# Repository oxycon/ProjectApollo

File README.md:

# ProjectApollo
This Github repository contains Designs/docs/software/PCB for Project Apollo (open source oxygen concentrator)

For more context behind the history/goals/motivation for this project please see our coverage in Helpful Engineering blog: 
- https://www.helpfulengineering.org/projects-news/project-spotlight-apollo-oxygen-concentrator/  

<b style='color:red'>Update</b>: check out our  presentation at RespiCon 2021! 
- https://github.com/oxycon/ProjectApollo/blob/master/docs/Project%20Apollo%20RespiCon%20v11.pdf

## Apollo v2 build instructions
- https://github.com/oxycon/ProjectApollo/blob/master/prototypes/Apollo%20v2/docs/Building%20instructions%20-%20prototype%20v2.pdf 

## Why
- Ventilators need oxygen! (typical FiO2 0.4 … 0.9)
- Oxygen generation is a big problem in developing countries. 
  - No established infrastructure. 
  - Oxygen bottles are expensive
- People are already looking at alternative (local) ways for producing oxygen
## What 
- Goal of the Apollo prototype = enabling people around the world to build the prototype as fast as possible
- Focus = Simplicity and speed of build 
- Final goal = Enable people to iterate and publish their own designs in the community
## How
- Follow the published build documentation
- Buy/source the materials (check out the BOM)
- Build the prototype
- Validate O2 concentration and flow. Use a good O2 and flow sensor. 
- Think about risk analysis and assessment: template for Apollo-derived design
- Document and iterate your own design. Publish your findings to the community! 

## Target 
- Output medical grade Oxygen ideally at 93% 
- Flow rate of 1-20 liters per minute (5 l/m being standard for oxygen therapy)

## Building instructions (prototype v2)
- Achieves O2 concentration out of the box: around 45% @ 5 liters/min (enough for less-critical ventilator use cases)
- Instructables-style (step-by-step) build instructions: https://github.com/oxycon/ProjectApollo/blob/master/prototypes/Apollo%20v2/docs/Building%20instructions%20-%20prototype%20v2.pdf 
- Bill of materials: https://github.com/oxycon/ProjectApollo/tree/master/prototypes/Apollo%20v2/BOM 

## Youtube videos
- Prototype v1 (old): https://www.youtube.com/playlist?list=PL34ykrB-qW7VGt1Hwd10Zb3s1eCDftkK8 
- Prototype v2 (latest): https://www.youtube.com/playlist?list=PL34ykrB-qW7X6d74_VnCFfBaVkm8pQXZK

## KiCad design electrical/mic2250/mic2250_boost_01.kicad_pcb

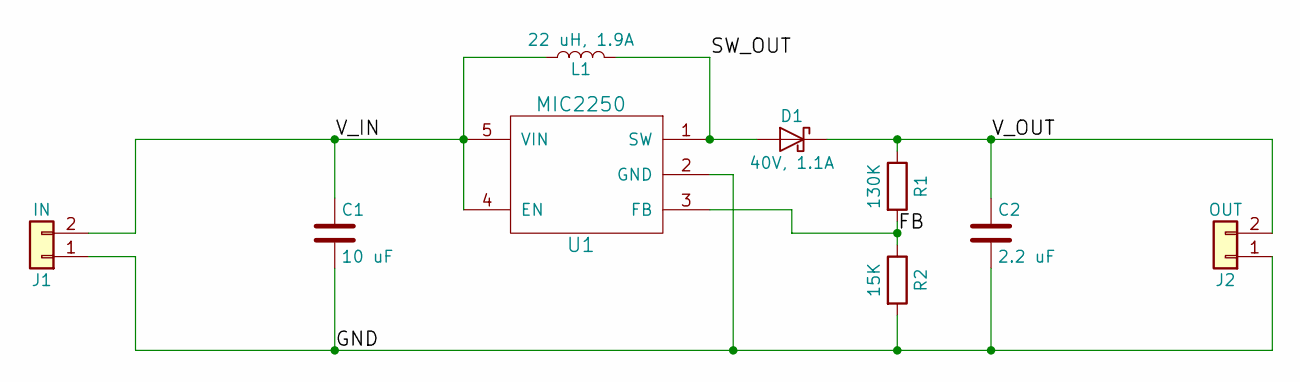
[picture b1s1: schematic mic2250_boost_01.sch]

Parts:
C1: 10 uF; C_1206
C2: 2.2 uF; C_1206
D1: 40V, 1.1A; do219ab
J1: IN; Pin_Header_Straight_1x02_Pitch2.54mm
J2: OUT; Pin_Header_Straight_1x02_Pitch2.54mm
L1: 22 uH, 1.9A; MURATA-DG6050C
R1: 130K; R_0805
R2: 15K; R_0805
U1: MIC2250; SOT-753_(TSOP-5)_Handsoldering

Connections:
/FB: R1.2, R2.1, U1.3 (FB)
/GND: C1.2, C2.2, J1.1, J2.1, R2.2, U1.2 (GND)
/SW_OUT: D1.2 (A), L1.2, U1.1 (SW)
/V_IN: C1.1, J1.2, L1.1, U1.4 (EN), U1.5 (VIN)
/V_OUT: C2.1, D1.1 (K), J2.2, R1.1

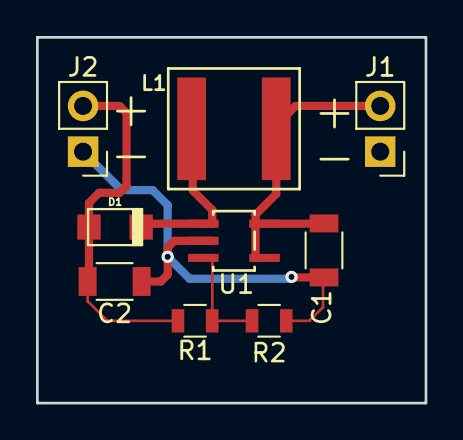
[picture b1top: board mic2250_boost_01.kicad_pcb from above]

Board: 2 copper layers, 21.6 x 20.3 mm, 9 parts (0 on the bottom side), 5 nets.

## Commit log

2020-03-18 add license
2020-03-20 Combined commit
2020-03-22 add Arduino source code for valve cycling
2020-03-22 move file in prototype subdirectory
2020-03-22 comments/fixes
2020-03-22 comments/fixes 2
2020-03-22 fix materials
2020-03-22 add schematic
2020-03-22 add PDF exports
2020-03-22 add more drawings, PDF
2020-03-22 move .scad file to Drawings
2020-03-22 Create disclaimer
2020-03-22 Update disclaimer
2020-03-22 add more text to drawings
2020-03-22 update video playlist
2020-03-22 add Invacare Platinum XL manuals
2020-03-22 move manuals in separate directory
2020-03-23 rename PDF manuals
2020-03-24 initial set of files with very little progress
2020-04-06 initial files
2020-04-07 add FAN support for Prototype v2
2020-04-07 add Gerber/SMTA order info for JLCPCB
2020-04-07 add picture
2020-04-08 initial drawings
2020-04-08 fixes/reorganization
2020-04-09 photos folder reorg
2020-04-09 reorg materials/BOM/drawings pdf
2020-04-09 move docs
2020-04-10 add Gasboard datasheets
2020-04-11 code for Arduino use of gasboard7500E, tested and working
2020-04-12 DIY version of PCB sort of done, require review
2020-04-12 bigger PCB preview image
2020-04-12 added more spare pins to i2c header
2020-04-12 fixed wrong battery type
2020-04-12 library added adafruit mprls
2020-04-12 changed to use Adafruit MPRLS
2020-04-12 added EOC signal to A0
2020-04-12 all components now top side
2020-04-13 added a fan header
2020-04-14 started to write some code
2020-04-14 added SPI signals to MPR breakout
2020-04-15 MPR 8x mux schematic and PCB
2020-04-15 add build instructions prototype v2
2020-04-16 work in progress code
2020-04-16 fixed chip select problem with mosfets
2020-04-16 minor doc fixes
2020-04-16 added 2x4 header to mpr-8x-mux pcb
2020-04-16 minor tweaks for ctrl pcb before fab
2020-04-16 ctrl pcb, more silk text, added extra ADC pins
2020-04-17 work in progress code (syntax fixes and tested some stuff)
2020-04-18 work in progress code (tested many functions)
2020-04-25 fix doc
2020-04-28 add O2 sensor Arduino code, check-in gerbers
2020-04-28 add better diagnostics
2020-04-28 add valve timing code and potentiometer hookup
2020-04-28 fix frequent timing change bug
2020-05-06 add PDF version of building v2 prototype
2020-05-06 add PDF version of building v2 prototype (2)
2020-05-08 add more info to README.md, other fixes
2020-05-15 add relief valve button
2020-05-17 add motorized valve Arduino code
2020-05-26 added TE MS5837 breakout PCB
2020-05-27 add gerbers to separate directory
2020-05-27 resize TE board, add mounting holes
2020-05-27 resize MPR board, add mounting holes
2020-05-27 move old Gerbers into dedicated directory
2020-05-27 add docs
2020-05-27 minor fixes (dimensions)
2020-05-27 add MPR sensor test code
2020-05-27 add ops risk analysis
2020-05-27 add BOM for apollo-ctrl
2020-05-31 making pressure sensor a lot more reliable
2020-06-02 add needle valve actuator and the MPR pressure together
2020-06-02 add PID control part 1
2020-06-02 PID controller works!
2020-06-06 add OLED display
2020-06-10 add rotary encoder to tweak target pressure
2020-06-14 minor fixes
2020-06-16 adding simulation code
2020-06-16 changed to md format
2020-06-16 better formatting of README
2020-07-10 add some docs
2020-07-11 Apollo v4 control board.docx
2020-07-16 add PPTs
2020-07-17 new changes
2020-07-17 new changes 2
2020-07-19 file reorg per prototype
2020-07-20 move Apollo v4 docs
2020-07-20 prototype v3 reorg
2020-07-20 initial doc for v4
2020-07-20 doc upgrades
2020-07-20 add PDFs
2020-07-28 add various docs
2020-07-28 add block diagram v4.01
2020-07-28 new PCB library with ESP32, LCD, and DRV8806
2020-07-29 [Early prototype for refactoring the simulation into a OpenAI gym-compatible API to represent the Apollo MDP][Non-sequential version][Need much more testing]
2020-07-29 Fixed import issues from parent directory
2020-07-29 Removing orifice controls from the actions space; action_space dim is now 2 corresponding to cycle_time and vent_time
2020-07-29 added bonsai stuff
2020-07-30 Start of V4 firmware
2020-07-30 Added Secrets.h, which is normally ignored
2020-07-30 Changing reward from prod_y to container_y
2020-07-30 Added serial port demo script
2020-07-30 template boards
2020-07-30 new version of template board
2020-07-30 fix template board symbols
2020-07-30 fix template board dimensions
2020-07-30 add HuskySat-1 credits
2020-07-30 simulator v1
2020-07-30 Start of display support
2020-07-30 re-added Secrets.h
2020-07-30 works with simulator
2020-07-30 merging to master of original
2020-07-30 Created a configurable non blocking state machine for the valve cycle.
2020-07-31 Control valves and concentrator from CLI
2020-07-31 Save state and more CLI commands
2020-07-31 - More CLI commands to configure WIFI and load preferences - CLI hex and binary parser - Moved valve pins - Removed EEPROM delays - Configure button pin
2020-07-31 Added Pinout document and libraries
2020-08-01 Added Oxygen Sensor logic
2020-08-01 Updated readme.txt with CLI commands
2020-08-01 Allow debug logging to be disabled
2020-08-02 Renamed TcpClient into TcpConnection and turned it into a Stream
2020-08-02 Allow debug stream to be taken over by TCP connection.
2020-08-02 Added document that suggest to use 2 types of zeolite
2020-08-02 Better debug status
2020-08-02 added support for valve drivers DRV-8806
2020-08-03 move connector bus to the edge of the board
2020-08-05 Initial version of the Apollo V4 modular valve board. No layout, and no header connections, pending pinout decisions with the controller board.
2020-08-05 Added commands to get configuration and sensor data as JSON.
2020-08-06 Added display brightness control
2020-08-06 Show sensor data on display
2020-08-07 Update display with sensor data
2020-08-07 Added BME280 humidity/pressure sensor
2020-08-07 Added Sensor base class
2020-08-08 Added SHTC3 humidity sensor
2020-08-08 Added HDC2080 humidity sensor
2020-08-08 Created sensor manager
2020-08-09 Added CLI humidity sensor support
2020-08-12 Fixed Valve SPI channel conflicting with LCD
2020-08-12 Cleaned up some unnecessary oxygen sensor logic + some small display bug fixes
2020-08-12 Added bar graphs for oxygen and flow
2020-08-12 Update valve board and proposed a pinout for Apollo v4
2020-08-14 Work on larger display ILI9488
2020-08-15 Added TCS34725 color sensor
2020-08-15 Drive valves from timer interrupt instrad of main loop to avoid jitter
2020-08-16 Changed DRV default count to 1 and SPI frequency to 10MHz
2020-08-16 Support non automatic Gasboard-7500E oxygen sensors
2020-08-18 PCB experiments
2020-08-19 more details for the Apollo v4
2020-08-19 rename Apollo v4 control board.docx -> Apollo v4 control box.docx
2020-08-19 add pdf version for Apollo v4 control box.pdf
2020-08-20 Added MPRLS pressure sensor and work on sensor management
2020-08-23 added HTU21D humidity sensor
2020-08-24 Start of error infrastructure + color sensor address config
2020-08-25 start of touch controller support + made date/time format configurable
2020-08-25 Results of crash investigation
2020-08-28 Initial version of the controller board, ESP32-PICO-KIT edition. Proposed GPIO mapping also updated in the document to break out all otherwise unused pins of the ESP32.
2020-08-28 work on error log, sensor errors, error infra
2020-08-29 fixes
2020-08-30 work on touch buttons + valve control buttons
2020-09-05 add 3.5 display sample files
2020-09-08 - Added CYCLE-DURATIONS command to get/set all durations at once - Additional pressure sensor error check - Increased oxygen sensor sample rate
2020-09-08 Renamed cycle to stage
2020-09-09 Added stats collection and stats logging
2020-09-09 Added concentrator data logging
2020-09-17 add Apollo v4 docs/presentation for COSMIC meeting
2020-09-17 add Apollo v4 docs/presentation for COSMIC meeting 2
2020-09-17 add Apollo v4 docs/presentation for COSMIC meeting 4
2020-09-17 add Apollo v4 docs/presentation for COSMIC meeting 5
2020-09-18 add Apollo v4 docs/presentation for COSMIC meeting 6
2020-09-24 add sample code
2020-10-31 add Oxikit presentation
2020-11-02 Work on self calibration
2020-11-02 Added disclaimer and license test
2020-11-02 Updated display library
2020-11-07 add PPT v08
2020-12-07 initial flow control code
2020-12-13 add more docs
2021-01-29 Update valve board schematic
2021-02-08 Remove stepper driver from Valve board to be moved to a future Stepper board
2021-03-09 add v09 ppt
2021-03-09 v09 ppt updates
2021-03-11 add Project Apollo - v09.pdf
2021-03-11 add license and gasboard code for the flow controller
2021-03-13 Add initial layout for the Valve board. Fully routed, with plenty of room to potentially add the steppers back
2021-03-14 add presentation @hack4good spring 2021
2021-03-19 Add stepper drivers to the valve board schematic. No guarantee that they fit, but if they do not another board can be made.
2021-03-20 moved simulation directory into its own repo - https://github.com/oxycon/ProjectApolloSimulation
2021-03-20 add README.md for simulation code pointing to its own repository
2021-03-23 Remove the Trinamics bipolar stepper drivers and add unipolar stepper drivers instead (as the motors are cheaper and more available).
2021-03-27 First layout pass for complete valve board
2021-03-29 Add PulseOximeterService to connect and read a BerryMed PulseOximeter
2021-03-29 Add file headers. Include PulseOximeterService into the v4 firmware
2021-04-01 Clean up valve board silkscreen and change diodes to SOD-123
2021-04-26 Enable Arduino Nano 33 support for PulseOximeterService
2021-04-28 Switch Apollo control board to use discrete SPI LCD and no M5-Stack
2021-04-28 Add buzzer to Apollo control board and move capacitor away from the USB port
2021-05-24 adding logos
2021-05-24 remove pdf copies
2021-05-28 add presentation for RespiCon 2021
2021-06-29 add JLCPCB DRU (inspired from OshPark)
2021-06-29 DRC error-free
2021-07-07 added Gerbers for control board v4 JLCPCB order
2021-07-07 added some docs
2021-07-07 added more docs
2021-08-26 make firmware compile for PICO
2021-08-27 add PICO port assignments
2021-09-26 Update TFT LCD pinout for version 2 of the Adafruit breakout board
2021-09-26 Add touch screen connectors on control PCB, and roll up fab to B
2021-11-18 disable wifi, sensors and the concentrator to prevent errors on barebone board
2021-11-18 add ESP32-PICO-KIT_V4.1 info
2021-12-24 making display work
2022-01-14 add DRV8803 sample code from TI
2022-02-12 remove lfs, add some jpg/pdf
2022-08-03 add mic2250
